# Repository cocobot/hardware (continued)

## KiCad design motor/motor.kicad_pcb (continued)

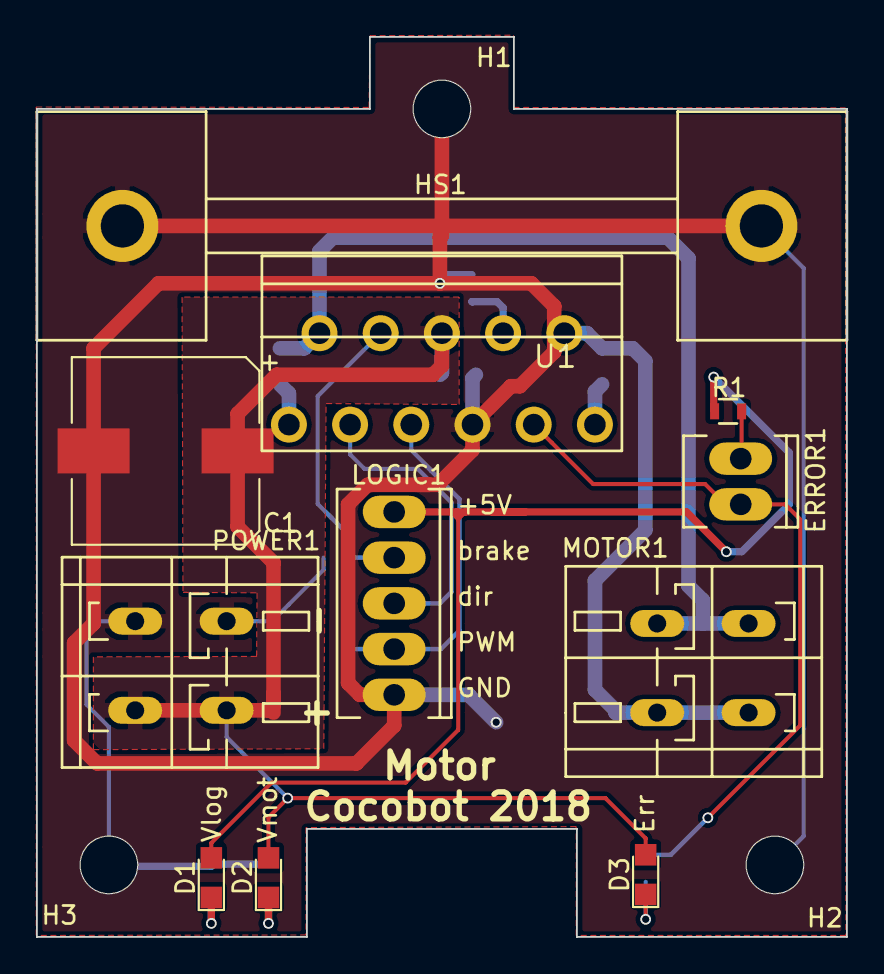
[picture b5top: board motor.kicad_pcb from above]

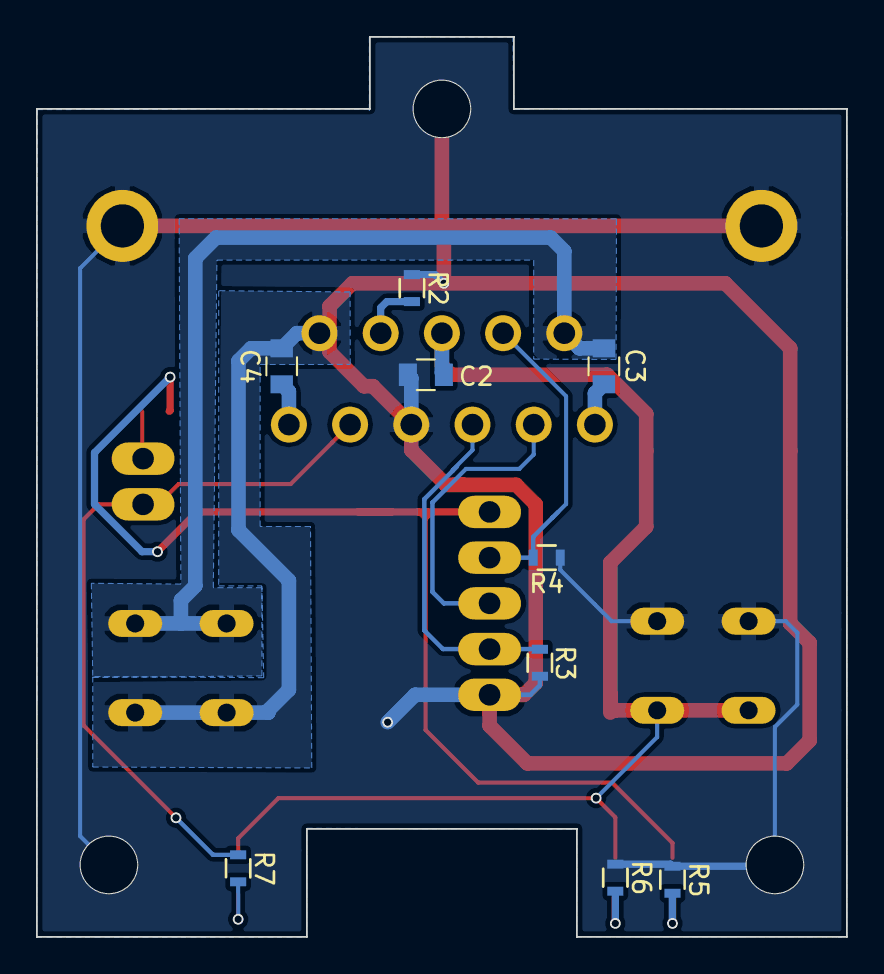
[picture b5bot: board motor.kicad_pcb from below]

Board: 2 copper layers, 45.0 x 50.0 mm, 23 parts (9 on the bottom side), 16 nets.

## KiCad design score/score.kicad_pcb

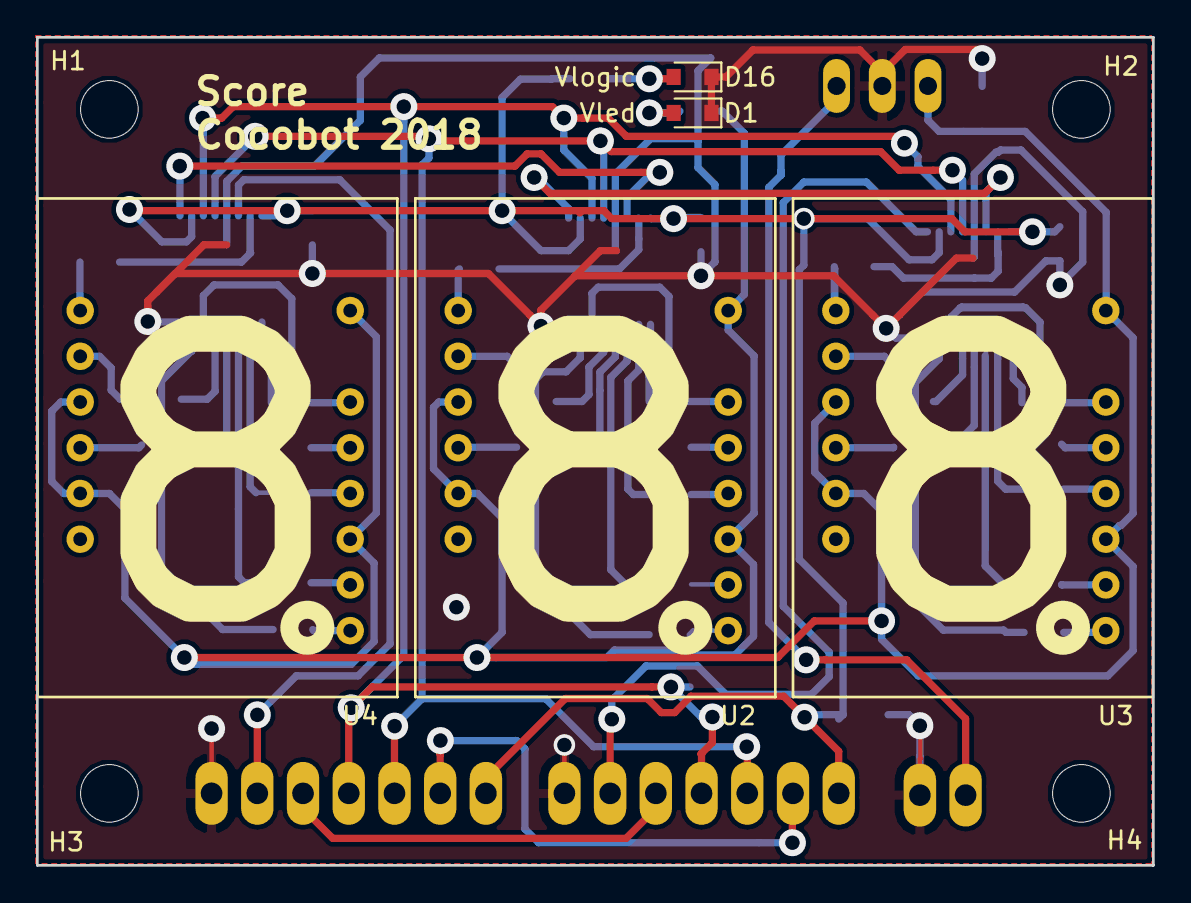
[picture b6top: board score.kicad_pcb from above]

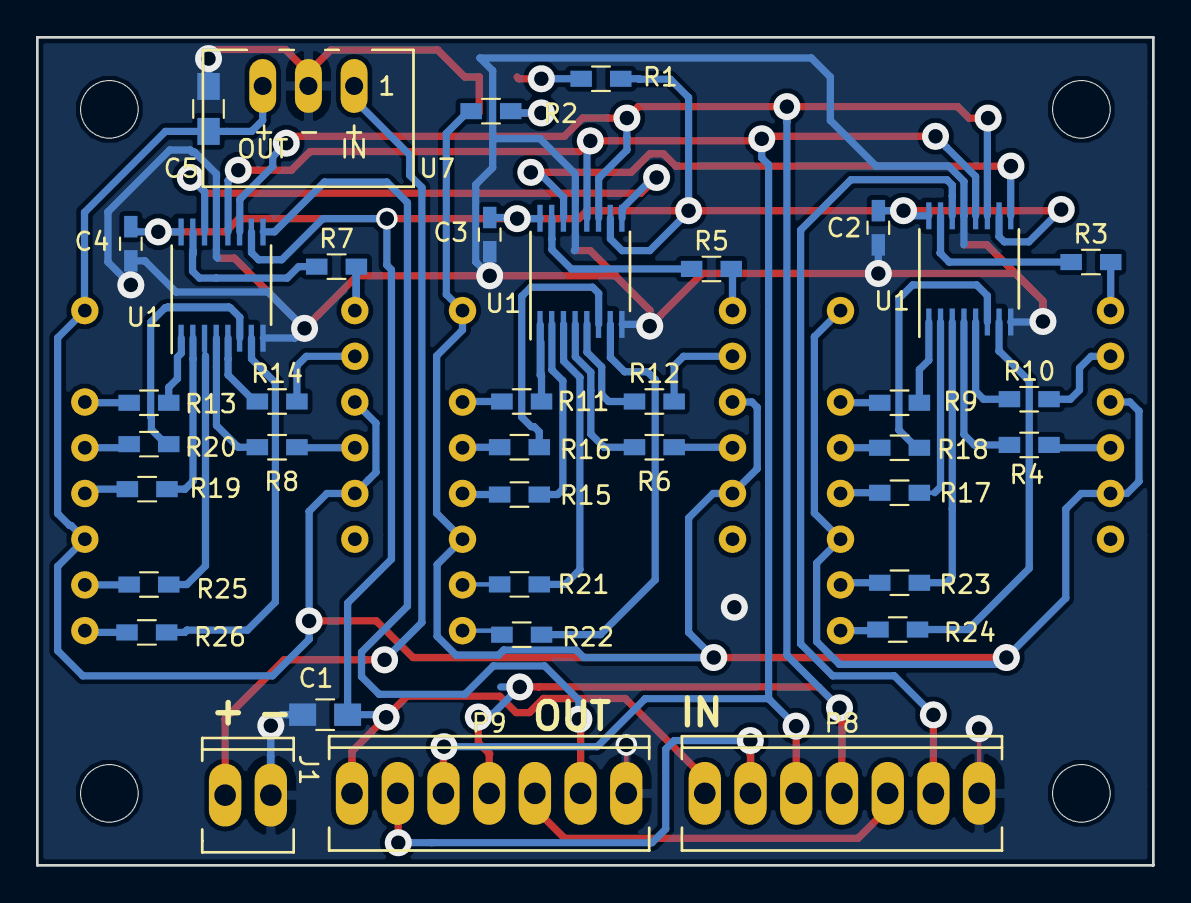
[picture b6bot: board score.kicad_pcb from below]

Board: 2 copper layers, 62.0 x 46.0 mm, 47 parts (38 on the bottom side), 43 nets.

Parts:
C1, C5: 10u; C_0805_HandSoldering
C2, C3, C4: 100n; C_0603_HandSoldering
D1, D16: LED; D_0805
H1, H2, H3, H4: CONN_01X01; MountingHole_3.2mm_M3
J1: Conn_01x02; Socket_MOLEX-KK-RM2-54mm_Lock_2pin_straight
P8, P9: CONN_01X07; Socket_MOLEX-KK-RM2-54mm_Lock_7pin_straight
R1, R2, R3, R4, R5, R6, R7, R8, R9, R10, R11, R12, R13, R14, R15, R16, R17, R18, R19, R20, R21, R22, R23, R24, R25, R26: 220; R_0603_HandSoldering
U1, U1#2, U1#3: 74HC595T16-13; TSSOP-16_4.4x5mm_Pitch0.65mm
U2, U3, U4: HDSP-C8A1
U7: TSR1-2433; TSR-1

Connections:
+3.3VP: C5.1, R2.1, U2.3, U2.5, U2.11, U2.16, U3.3, U3.5, U3.11, U3.16, U4.3, U4.5, U4.11, U4.16, U7.3
+3V3: C1.1, C2.1, C3.1, C4.1, P8.1, P9.1, R1.1, U1#3.10, U1#3.16
/ch0_3v3: R3.2, U1#3.15
/ch1_3v3: R9.2, U1#3.1
/ch2_3v3: R17.2, U1#3.2
/ch3_3v3: R23.2, U1#3.3
/ch4_3v3: R4.2, U1#3.4
/ch5_3v3: R10.2, U1#3.5
/ch6_3v3: R18.2, U1#3.6
/ch7_3v3: R24.2, U1#3.7
/load_input_3v3: P8.2, P9.2
/miso_3v3: P8.5, P9.5
/mosi_3v3: P8.6, U1#3.14
/sck_3v3: P8.4, P9.4, U1#3.11
/set_output_3v3: P8.3, P9.3, U1#3.12
GND: C1.2, C2.2, C3.2, C4.2, C5.2, D1.1, D16.1, J1.2, P8.7, P9.7, U1#3.8, U1#3.13, U7.2
unnamed: D1.2, R2.2
unnamed: D16.2, R1.2
unnamed: J1.1, U7.1
unnamed: R3.1, U4.1
unnamed: R4.1, U4.4
unnamed: R5.1, U2.1
unnamed: R6.1, U2.4
unnamed: R7.1, U3.1
unnamed: R8.1, U3.4
unnamed: R9.1, U4.14
unnamed: R10.1, U4.2
unnamed: R11.1, U2.14
unnamed: R12.1, U2.2
unnamed: R13.1, U3.14
unnamed: R14.1, U3.2
unnamed: R15.1, U2.12
unnamed: R16.1, U2.13
unnamed: R17.1, U4.12
unnamed: R18.1, U4.13
unnamed: R19.1, U3.12
unnamed: R20.1, U3.13
unnamed: R21.1, U2.10
unnamed: R22.1, U2.9
unnamed: R23.1, U4.10
unnamed: R24.1, U4.9
unnamed: R25.1, U3.10
unnamed: R26.1, U3.9

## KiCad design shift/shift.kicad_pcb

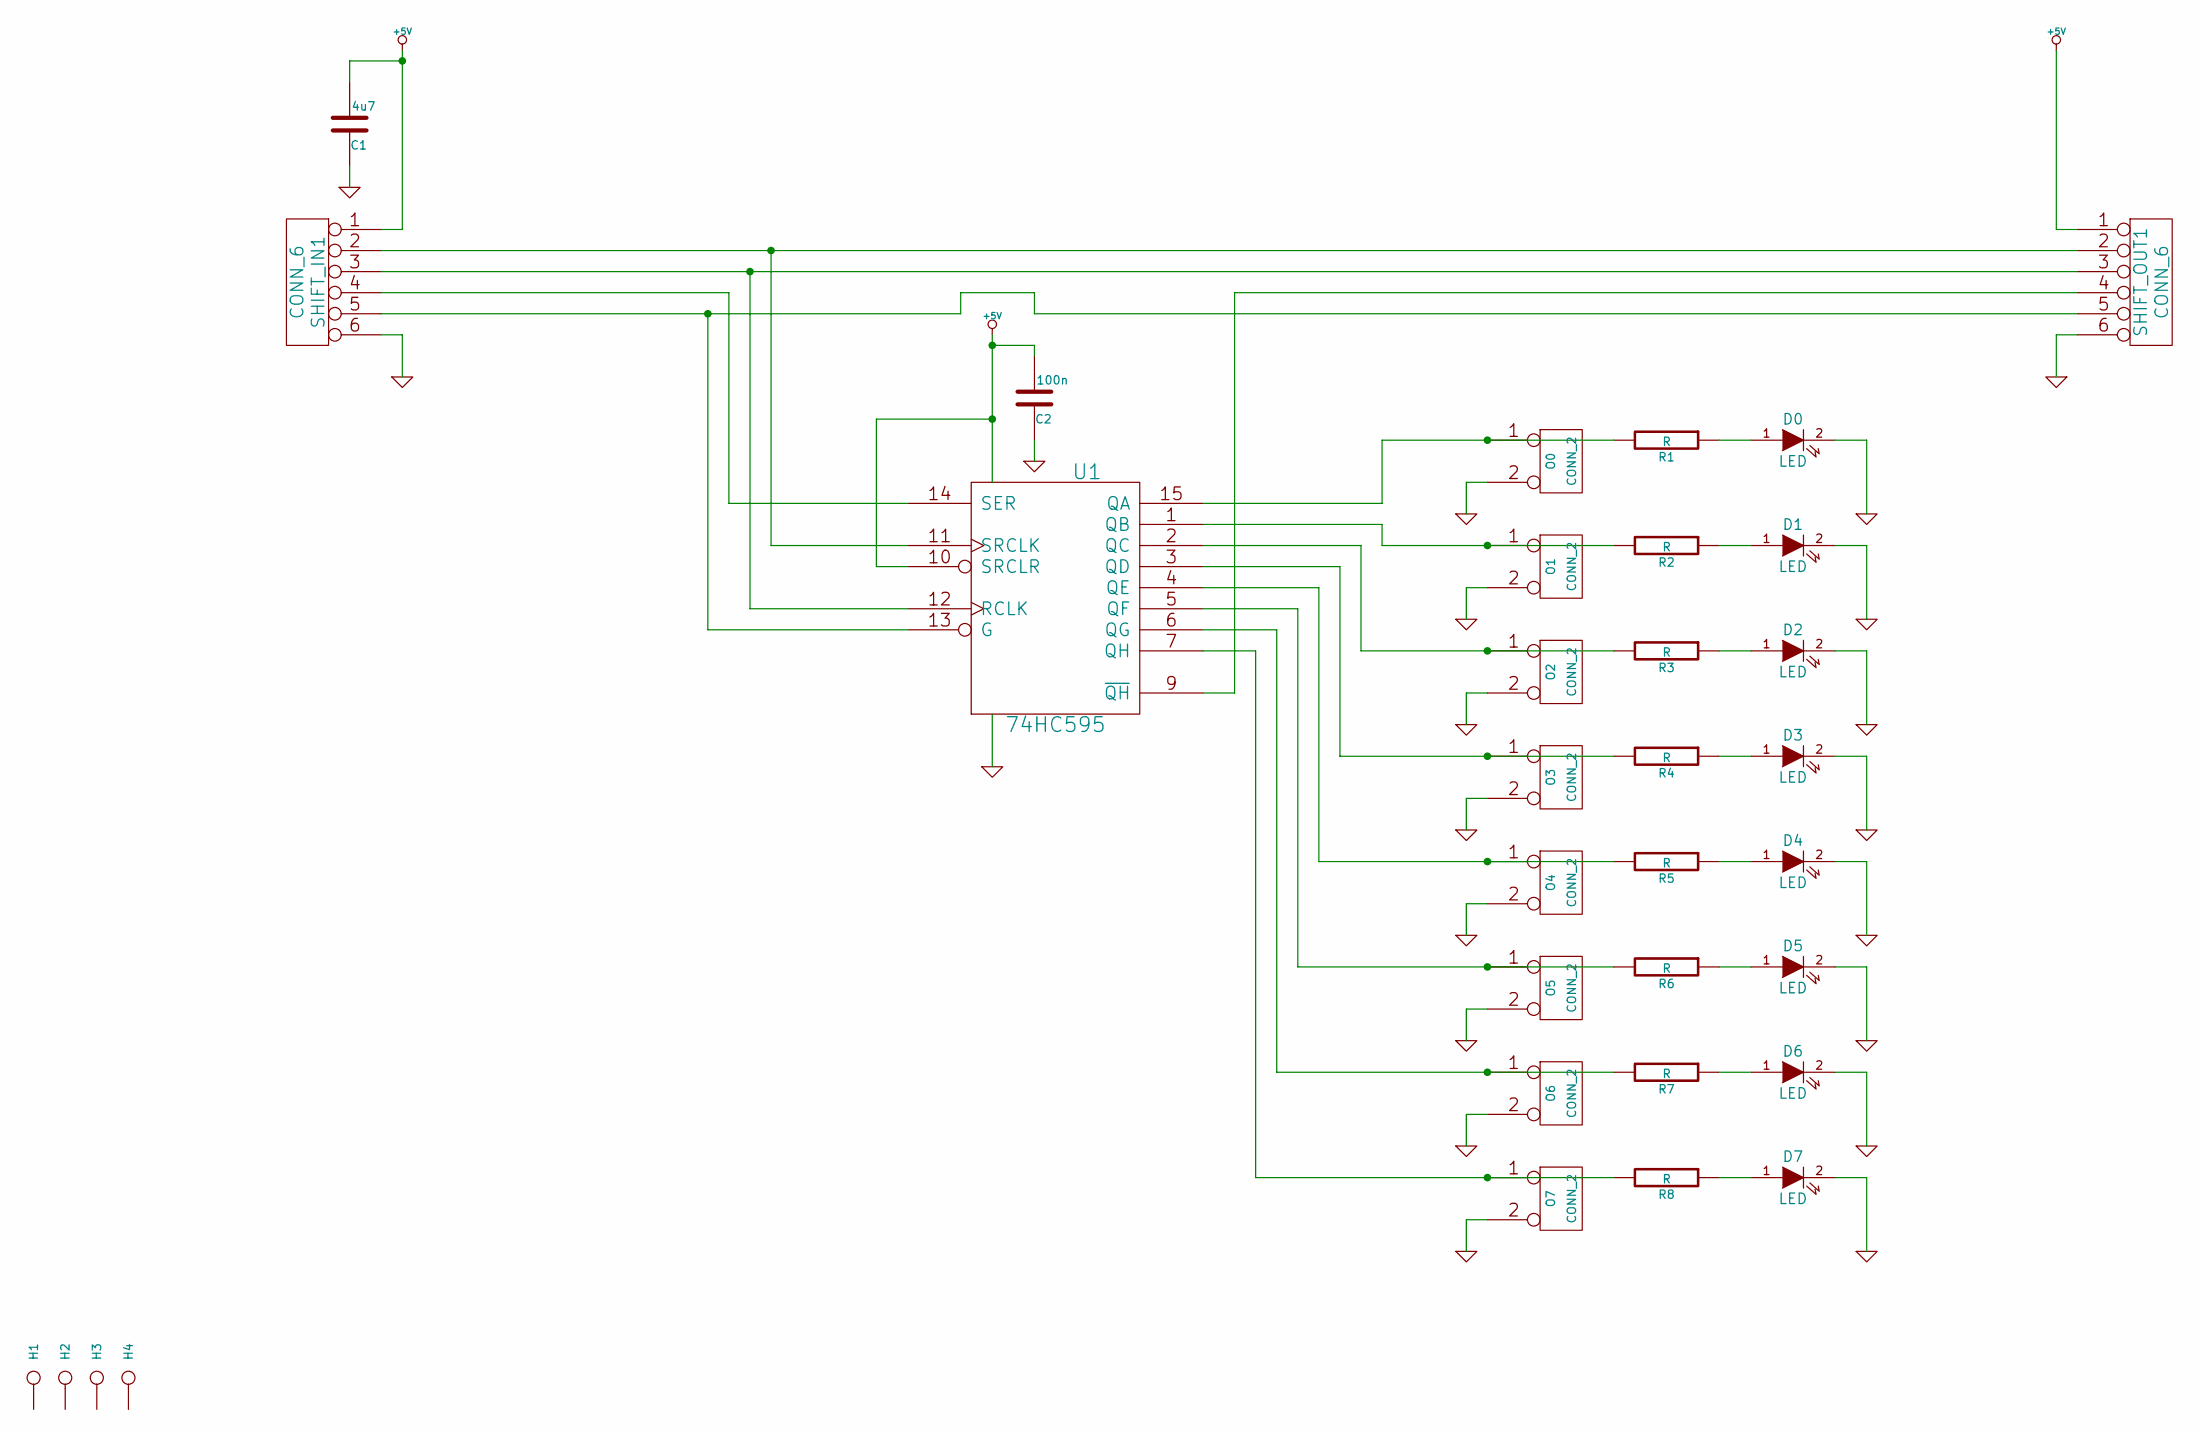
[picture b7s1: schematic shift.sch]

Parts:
C1: 4u7; C_0603
C2: 100n; C_0603
D0, D1, D2, D3, D4, D5, D6, D7: LED; LED-0603
H1, H2, H3, H4: CONN_1; MountingHole_3-5mm
O0, O1, O2, O3, O4, O5, O6, O7: CONN_2; Socket_MOLEX-KK-RM2-54mm_Lock_2pin_straight
R1, R2, R3, R4, R5, R6, R7, R8: R; R_0603
SHIFT_IN1: CONN_6; Socket_MOLEX-KK-RM2-54mm_Lock_6pin_straight
SHIFT_OUT1: CONN_6; Socket_MOLEX-KK-RM2-54mm_Lock_6pin_straight
U1: 74HC595; TSSOP-16_4.4x5mm_Pitch0.65mm

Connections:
GND: C1.1, C2.1, D0.2 (K), D1.2 (K), D2.2 (K), D3.2 (K), D4.2 (K), D5.2 (K), D6.2 (K), D7.2 (K), O0.2 (PM), O1.2 (PM), O2.2 (PM), O3.2 (PM), O4.2 (PM), O5.2 (PM), O6.2 (PM), O7.2 (PM), SHIFT_IN1.6, SHIFT_OUT1.6, U1.8 (GND); also elsewhere on the board
unnamed: D0.1 (A), R1.1
unnamed: D1.1 (A), R2.1
unnamed: D2.1 (A), R3.1
unnamed: D3.1 (A), R4.1
unnamed: D4.1 (A), R5.1
unnamed: D5.1 (A), R6.1
unnamed: D6.1 (A), R7.1
unnamed: D7.1 (A), R8.1
unnamed: O0.1, R1.2, U1.15 (QA)
unnamed: O1.1, R2.2, U1.1 (QB)
unnamed: O2.1, R3.2, U1.2 (QC)
unnamed: O3.1, R4.2, U1.3 (QD)
unnamed: O4.1, R5.2, U1.4 (QE)
unnamed: O5.1, R6.2, U1.5 (QF)
unnamed: O6.1, R7.2, U1.6 (QG)
unnamed: O7.1, R8.2, U1.7 (QH)
unnamed 21: SHIFT_IN1.2, SHIFT_OUT1.2, U1.11 (SRCLK); also elsewhere on the board
unnamed 22: SHIFT_IN1.3, SHIFT_OUT1.3, U1.12 (RCLK); also elsewhere on the board
unnamed 23: SHIFT_IN1.4, U1.14 (SER); also elsewhere on the board
unnamed 24: SHIFT_IN1.5, SHIFT_OUT1.5, U1.13 (G); also elsewhere on the board
unnamed 25: SHIFT_OUT1.4, U1.9 (~QH); also elsewhere on the board
VCC: C1.2, C2.2, SHIFT_IN1.1, SHIFT_OUT1.1, U1.10 (SRCLR), U1.16 (VCC); also elsewhere on the board

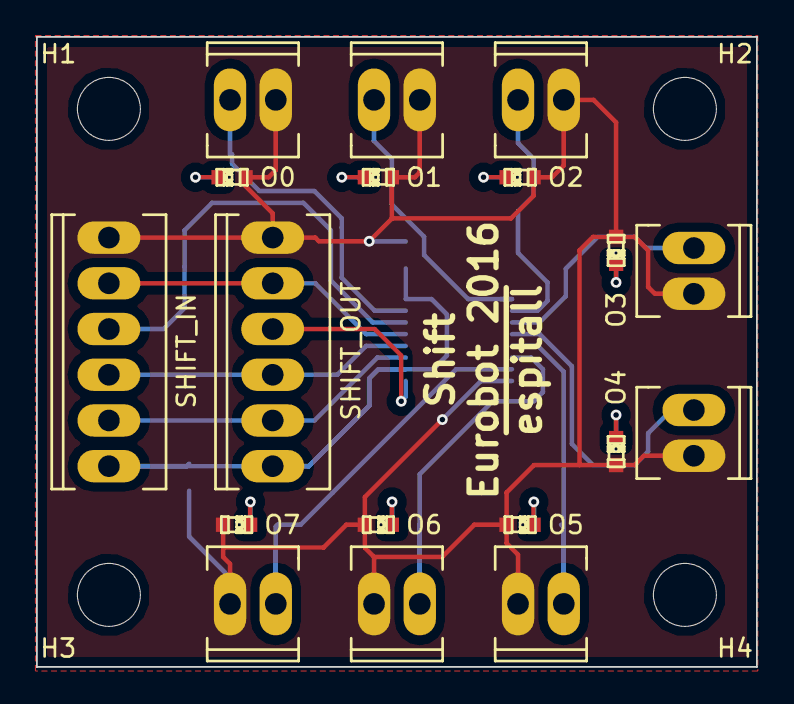
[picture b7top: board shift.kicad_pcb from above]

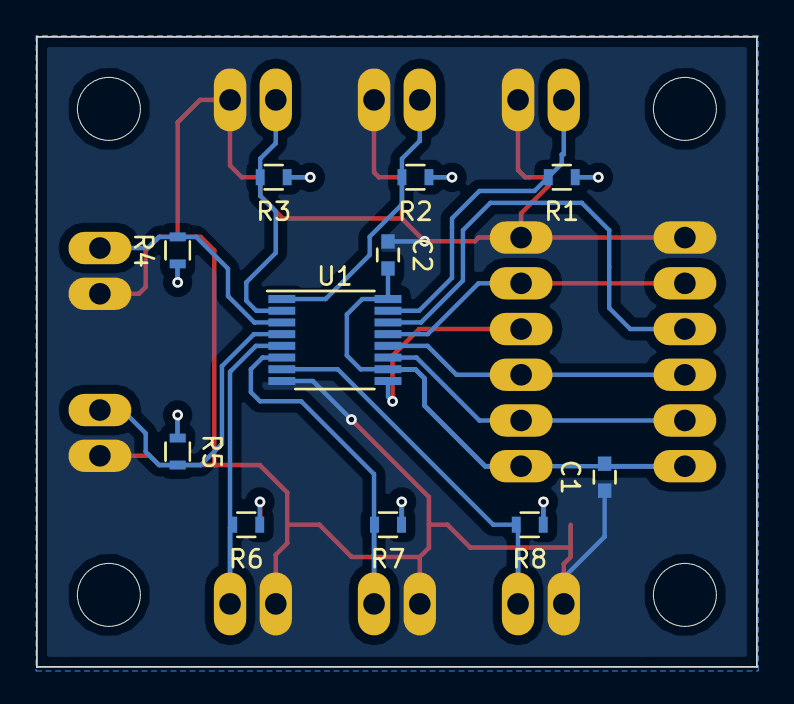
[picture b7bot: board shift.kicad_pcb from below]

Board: 2 copper layers, 40.0 x 35.0 mm, 33 parts (11 on the bottom side), 23 nets.

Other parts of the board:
SHIFT_IN: CONN_6; Socket_MOLEX-KK-RM2-54mm_Lock_6pin_straight
SHIFT_OUT: CONN_6; Socket_MOLEX-KK-RM2-54mm_Lock_6pin_straight

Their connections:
GND: SHIFT_IN.6, SHIFT_OUT.6; also elsewhere on the board
unnamed 21: SHIFT_IN.2, SHIFT_OUT.2; also elsewhere on the board
unnamed 22: SHIFT_IN.3, SHIFT_OUT.3; also elsewhere on the board
unnamed 23: SHIFT_IN.4; also elsewhere on the board
unnamed 24: SHIFT_IN.5, SHIFT_OUT.5; also elsewhere on the board
unnamed 25: SHIFT_OUT.4; also elsewhere on the board
VCC: SHIFT_IN.1, SHIFT_OUT.1; also elsewhere on the board
